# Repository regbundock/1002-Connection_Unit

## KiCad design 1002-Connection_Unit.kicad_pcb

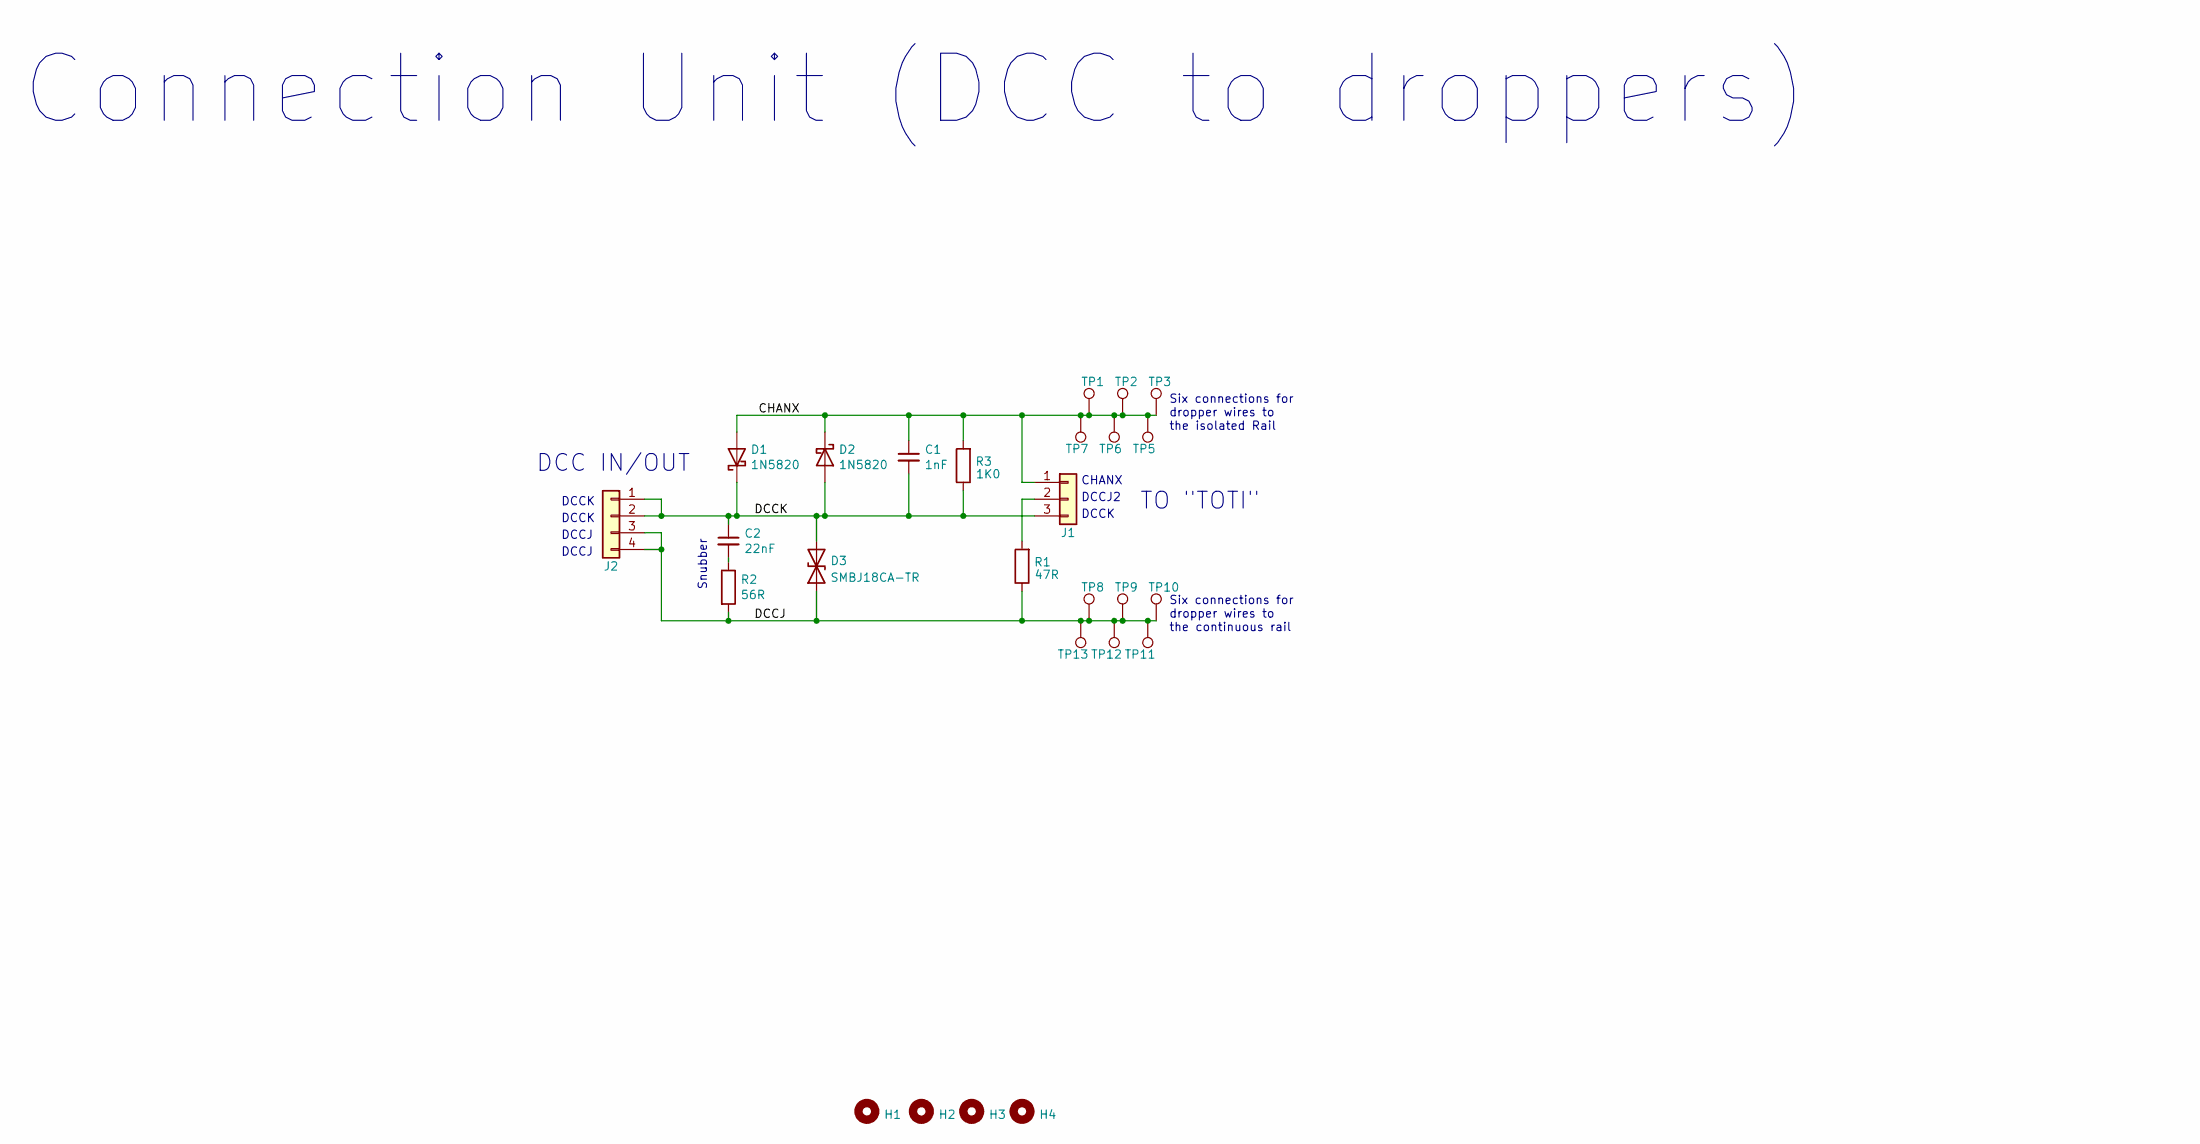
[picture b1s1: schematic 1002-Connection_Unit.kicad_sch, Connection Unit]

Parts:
C1: 1nF; C_Disc_D4.3mm_W1.9mm_P5.00mm
C2: 22nF; C_Rect_L7.2mm_W2.5mm_P5.00mm_FKS2_FKP2_MKS2_MKP2
D1, D2: 1N5820; D_DO-201AD_P15.24mm_Horizontal
D3: SMBJ18CA-TR; D_SMB_Handsoldering
H1, H2, H3, H4: MountingHole; MountingHole_3.2mm_M3_Pad_TopBottom
J1: Conn_01x03; Molex_KK-254_AE-6410-03A_1x03_P2.54mm_Vertical
J2: Conn_01x04; Molex_KK-396_A-41791-0004_1x04_P3.96mm_Vertical
R1: 47R; R_Axial_DIN0207_L6.3mm_D2.5mm_P10.16mm_Horizontal
R2: 56R; R_Axial_DIN0207_L6.3mm_D2.5mm_P10.16mm_Horizontal
R3: 1K0; R_Axial_DIN0207_L6.3mm_D2.5mm_P10.16mm_Horizontal
TP1, TP2, TP3, TP5, TP6, TP7, TP8, TP9, TP10, TP11, TP12, TP13: TestPoint; TestPoint_THTPad_2.5x2.5mm_Drill1.2mm

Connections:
/CHANX: C1.1, D1.2 (A), D2.1 (K), J1.1, R3.2, TP1.1, TP2.1, TP3.1, TP5.1, TP6.1, TP7.1
/DCCJ: D3.1 (A1), J2.3, J2.4, R1.1, R2.2, TP8.1, TP9.1, TP10.1, TP11.1, TP12.1, TP13.1
/DCCK: C1.2, C2.1, D1.1 (K), D2.2 (A), D3.2 (A2), J1.3, J2.1, J2.2, R3.1
unnamed: C2.2, R2.1
unnamed: J1.2, R1.2

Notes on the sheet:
DCCK
TO "TOTI"
Six connections for dropper wires to the continuous rail
Six connections for dropper wires to the isolated Rail
DCCJ
CHANX
DCCJ2
Snubber
Connection Unit (DCC to droppers)
DCC IN/OUT

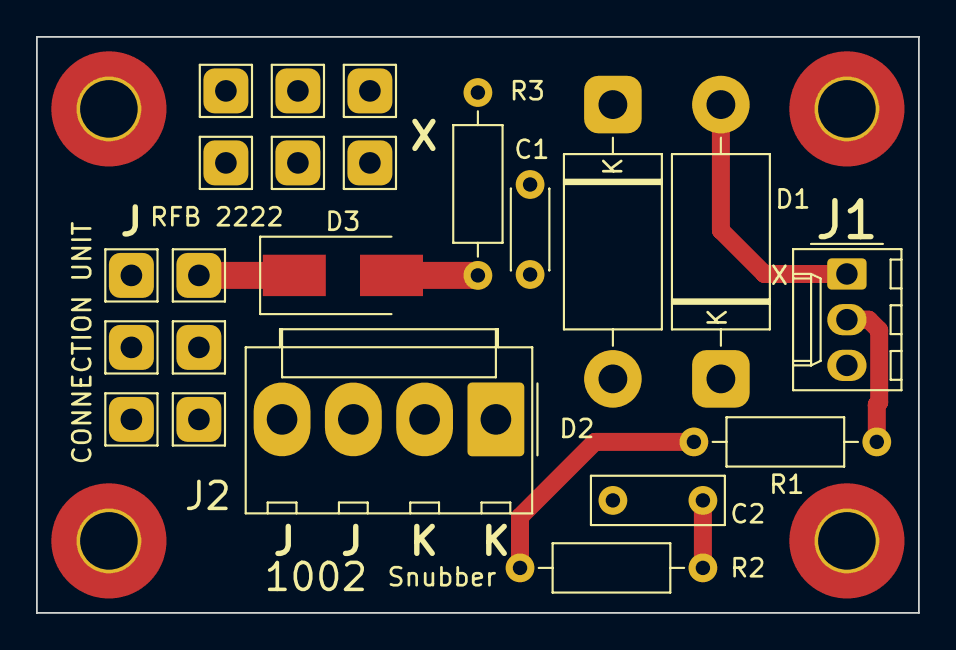
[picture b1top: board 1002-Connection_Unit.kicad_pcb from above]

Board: 2 copper layers, 49.0 x 32.0 mm, 26 parts (0 on the bottom side), 5 nets.
